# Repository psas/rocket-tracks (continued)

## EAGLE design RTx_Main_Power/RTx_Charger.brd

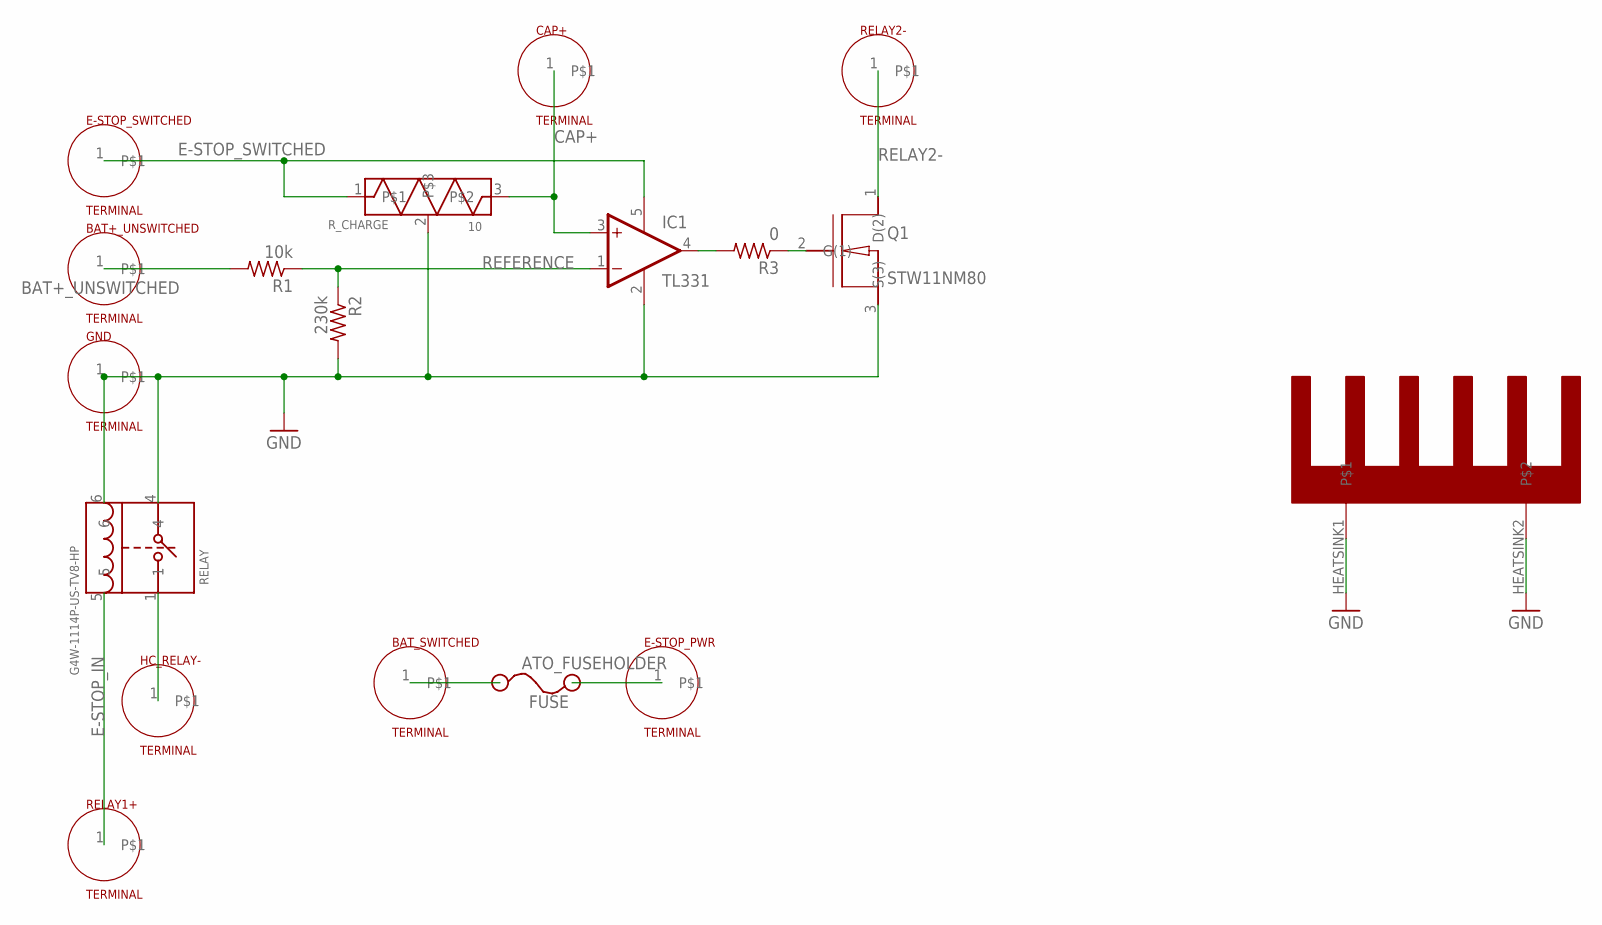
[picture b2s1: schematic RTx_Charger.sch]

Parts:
BAT+_UNSWITCHED: TERMINAL; TERMINAL_STUD
BAT_SWITCHED: TERMINAL; TERMINAL_NO-STUD
CAP+: TERMINAL; TERMINAL_STUD
E-STOP_PWR: TERMINAL; TERMINAL_STUD
E-STOP_SWITCHED: TERMINAL; TERMINAL_NO-STUD
FUSE: ATO_FUSEHOLDER; ATO_BLADE_FUSE
GND: TERMINAL; TERMINAL_STUD
HC_RELAY-: TERMINAL; TERMINAL_NO-STUD
HEATSINK: WA-T247-101E
IC1: TL331; DBV-R-PDSO-G5
Q1: STW11NM80; TO-247
R1: 10k; R1206
R2: 230k; R1206
R3: 0; R1206
RELAY: G4W-1114P-US-TV8-HP
RELAY1+, RELAY2-: TERMINAL; TERMINAL_NO-STUD
R_CHARGE: 10; TEH70

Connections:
BAT+_UNSWITCHED: BAT+_UNSWITCHED.1, R1.2
BAT_SWITCHED: BAT_SWITCHED.1, FUSE.2.1 (C), FUSE.2.2 (C), FUSE.2.3 (C), FUSE.2.4 (C)
CAP+: CAP+.1, IC1.3 (+IN), R_CHARGE.3
E-STOP_IN: RELAY.5, RELAY1+.1
E-STOP_PWR: E-STOP_PWR.1, FUSE.1.1 (A), FUSE.1.2 (A), FUSE.1.3 (A), FUSE.1.4 (A)
E-STOP_SWITCHED: E-STOP_SWITCHED.1, IC1.5 (V+), R_CHARGE.1
GND: GND.1, HEATSINK.HEATSINK1, HEATSINK.HEATSINK2, IC1.2 (GND), Q1.3 (S(3)), R2.2, RELAY.4, RELAY.6, R_CHARGE.2
HC_RELAY-: HC_RELAY-.1, RELAY.1
unnamed: IC1.4 (OUT), R3.2
unnamed: Q1.2 (G(1)), R3.1
REFERENCE: IC1.1 (-IN), R1.1, R2.1
RELAY2-: Q1.1 (D(2)), RELAY2-.1

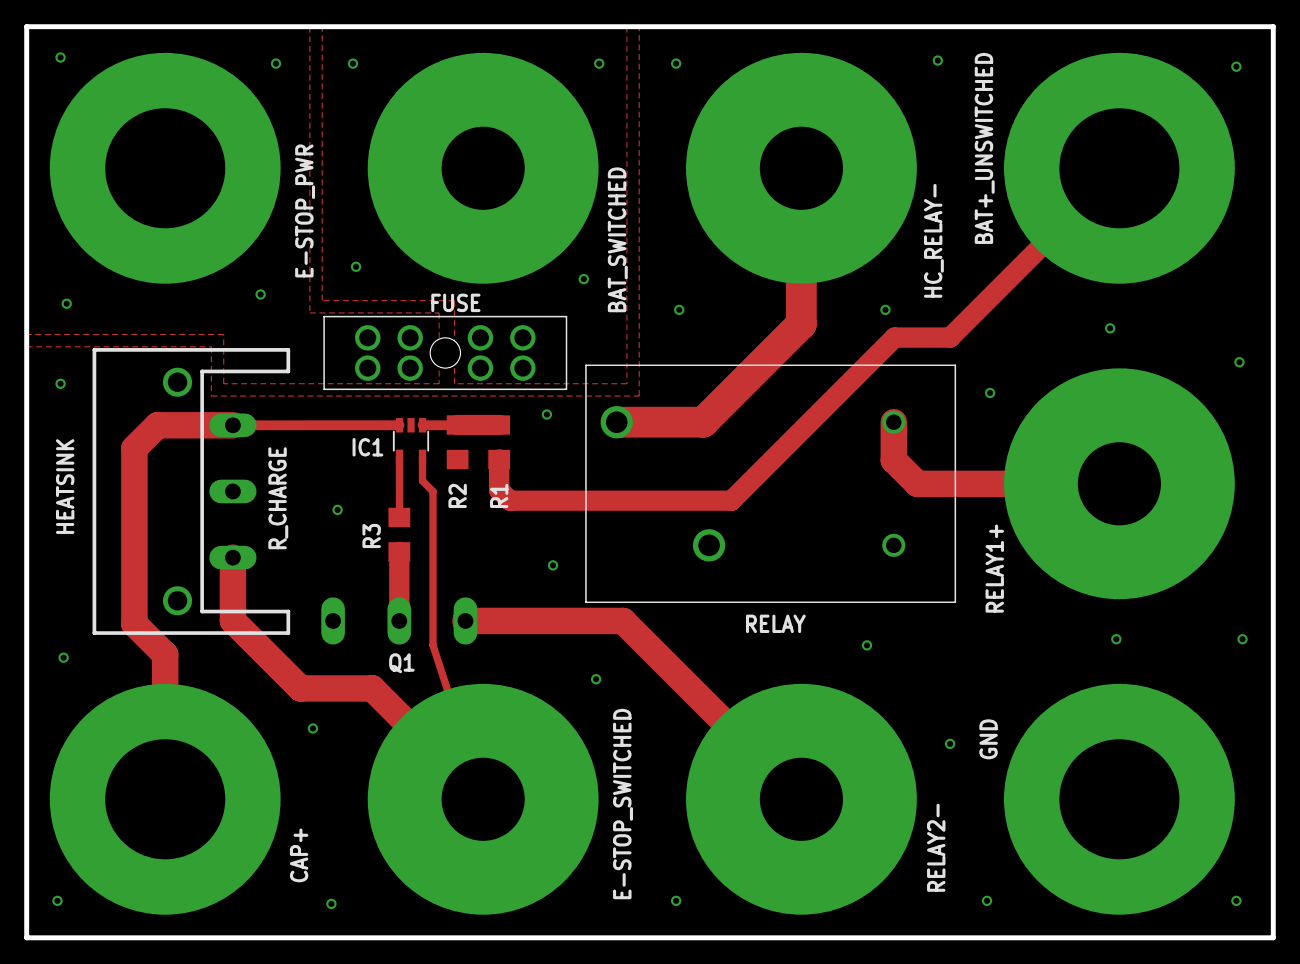
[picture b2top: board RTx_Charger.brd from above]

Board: 2 copper layers, 102.9 x 75.2 mm, 18 parts (0 on the bottom side), 12 nets.

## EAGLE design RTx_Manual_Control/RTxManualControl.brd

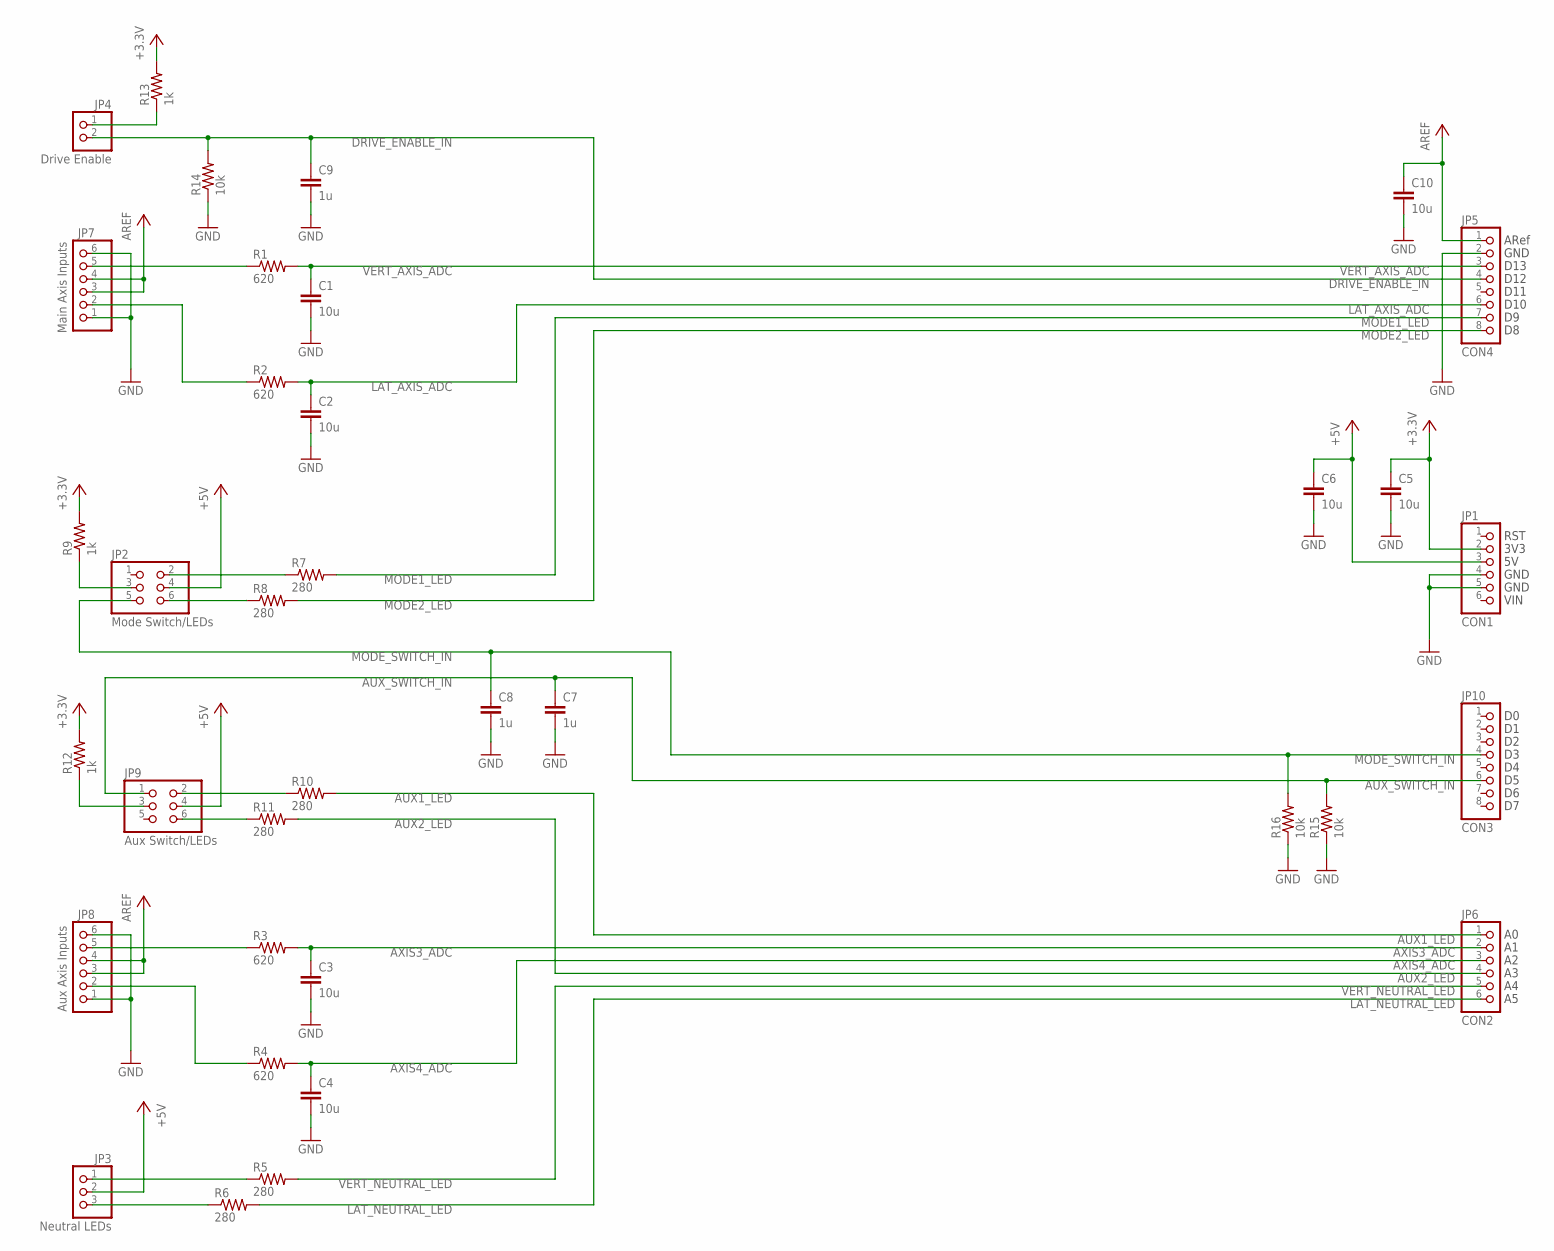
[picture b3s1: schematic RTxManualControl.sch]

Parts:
C1, C2, C3, C4, C5, C6, C10: 10u; C1206
C7, C8, C9: 1u; C1206
JP1: CON1; 1X06
JP2: Mode Switch/LEDs; 2X03
JP3: Neutral LEDs; 1X03
JP4: Drive Enable; 1X02
JP5: CON4; 1X08
JP6: CON2; 1X06
JP7: Main Axis Inputs; 1X06
JP8: Aux Axis Inputs; 1X06
JP9: Aux Switch/LEDs; 2X03
JP10: CON3; 1X08
R1, R2, R3, R4: 620; R1206
R5, R6, R7, R8, R10, R11: 280; R1206
R9, R12, R13: 1k; R1206
R14, R15, R16: 10k; R1206

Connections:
+3.3V: C5.1, JP1.2, R9.2, R12.2, R13.2
+5V: C6.1, JP1.3, JP2.4, JP3.2, JP9.4
AREF: C10.1, JP5.1, JP7.3, JP7.4, JP8.3, JP8.4
AUX1_LED: JP6.1, R10.2
AUX1_LED_CONN: JP9.2, R10.1
AUX2_LED: JP6.4, R11.2
AUX2_LED_CONN: JP9.6, R11.1
AUX_SWITCH_IN: C7.1, JP9.1, JP10.6, R15.2
AUX_SWITCH_PULLUP: JP9.3, R12.1
AXIS3_ADC: C3.1, JP6.2, R3.2
AXIS3_CONN: JP8.5, R3.1
AXIS4_ADC: C4.1, JP6.3, R4.2
AXIS4_CONN: JP8.2, R4.1
DRIVE_ENABLE_IN: C9.1, JP4.2, JP5.4, R14.2
DRIVE_ENABLE_PULLUP: JP4.1, R13.1
GND: C1.2, C2.2, C3.2, C4.2, C5.2, C6.2, C7.2, C8.2, C9.2, C10.2, JP1.4, JP1.5, JP5.2, JP7.1, JP7.6, JP8.1, JP8.6, R14.1, R15.1, R16.1
LAT_AXIS_ADC: C2.1, JP5.6, R2.2
LAT_AXIS_CONN: JP7.2, R2.1
LAT_NEAUTRAL_LED_CONN: JP3.3, R6.1
LAT_NEUTRAL_LED: JP6.6, R6.2
MODE1_LED: JP5.7, R7.2
MODE1_LED_CONN: JP2.2, R7.1
MODE2_LED: JP5.8, R8.2
MODE2_LED_CONN: JP2.6, R8.1
MODE_SWITCH_IN: C8.1, JP2.5, JP10.4, R16.2
MODE_SWITCH_PULLUP: JP2.3, R9.1
VERT_AXIS_ADC: C1.1, JP5.3, R1.2
VERT_AXIS_CONN: JP7.5, R1.1
VERT_NEUTRAL_LED: JP6.5, R5.2
VERT_NEUTRAL_LED_CONN: JP3.1, R5.1

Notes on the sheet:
ARef
GND
D13
D12
D11
D10
RST
3V3
VIN

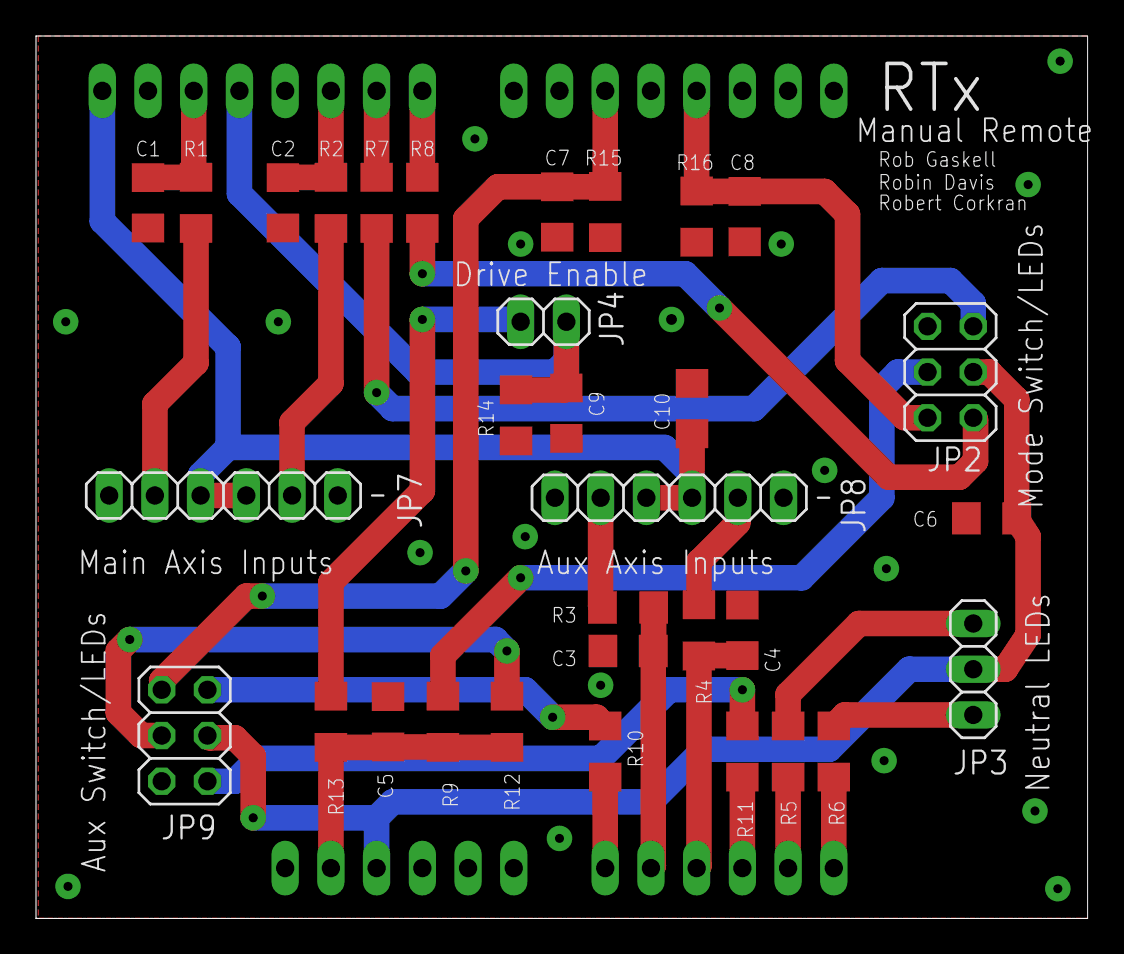
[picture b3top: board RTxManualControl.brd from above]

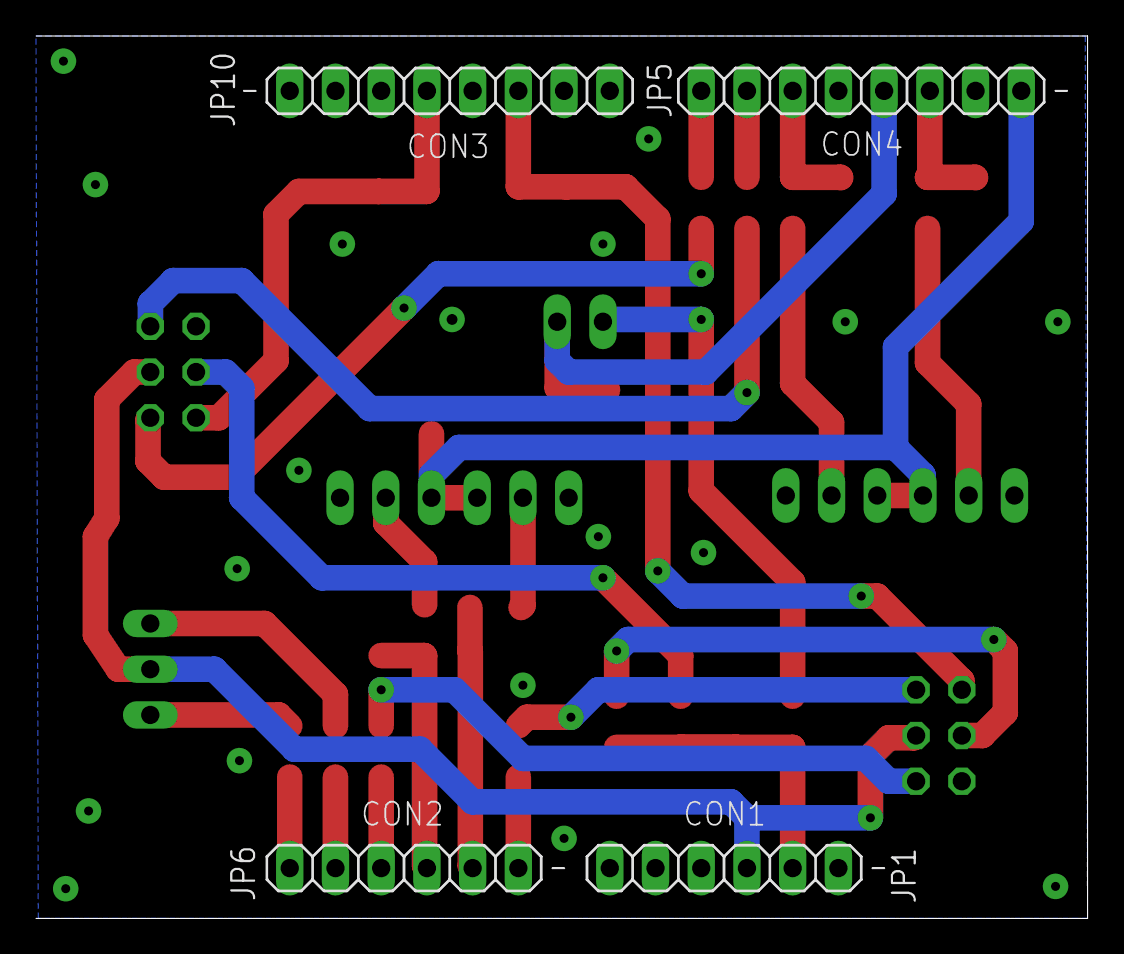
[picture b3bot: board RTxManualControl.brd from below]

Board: 2 copper layers, 58.4 x 49.0 mm, 36 parts (4 on the bottom side), 30 nets.

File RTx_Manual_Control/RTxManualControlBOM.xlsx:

RTx ID | Qty | Order PN | Value | Device | Package | Parts | Description
 | 7 |  | 10u | C-EUC1206 | C1206 | C1, C2, C3, C4, C5, C6, C10 | CAPACITOR, European symbol
 | 3 |  | 1u | C-EUC1206 | C1206 | C7, C8, C9 | CAPACITOR, European symbol
 | 3 |  | 10k | R-US_R1206 | R1206 | R14, R15, R16 | RESISTOR, American symbol
 | 3 |  | 1k | R-US_R1206 | R1206 | R9, R12, R13 | RESISTOR, American symbol
 | 6 |  | 280 | R-US_R1206 | R1206 | R5, R6, R7, R8, R10, R11 | RESISTOR, American symbol
 | 4 |  | 620 | R-US_R1206 | R1206 | R1, R2, R3, R4 | RESISTOR, American symbol
 | 2 |  |  | PINHD-1X6 | 1X06 | JP1, JP6 | PIN HEADER
 | 2 |  |  | PINHD-1X8 | 1X08 | JP5, JP10 | PIN HEADER
 | 1 |  | Drive Enable | PINHD-1X2 | 1X02 | JP4 | PIN HEADER
 | 2 |  |  | PINHD-1X6 Polarized | 1X06 | JP7, JP8 | PIN HEADER POLARIZED
 | 2 |  |  | PINHD-2X3 Polarized | 2X03 | JP2, JP9 | PIN HEADER POLARIZED
 | 1 |  | Neutral LEDs | PINHD-1X3 Polarized | 1X03 | JP3 | PIN HEADER POLARIZED

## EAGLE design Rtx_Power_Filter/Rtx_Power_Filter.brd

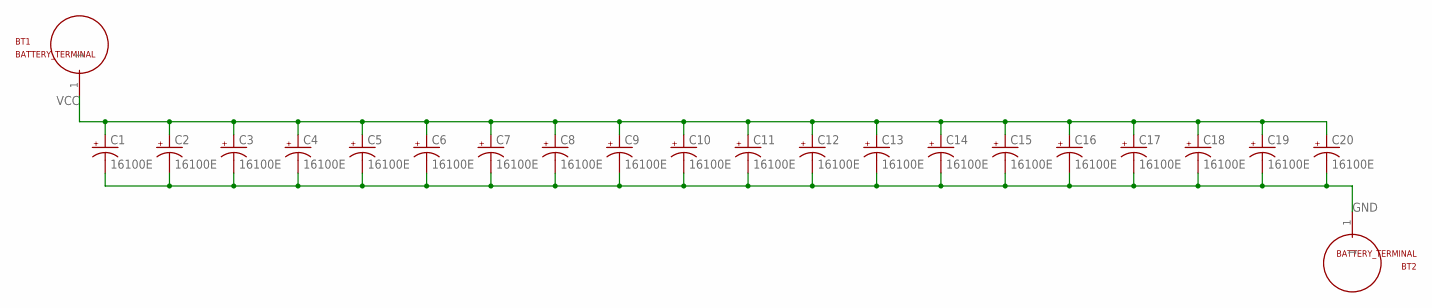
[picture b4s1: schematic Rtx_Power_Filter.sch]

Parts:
BT1, BT2: BATTERY_TERMINAL
C1, C2, C3, C4, C5, C6, C7, C8, C9, C10, C11, C12, C13, C14, C15, C16, C17, C18, C19, C20: 16100E; 16100

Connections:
GND: BT2.1, C1.-, C2.-, C3.-, C4.-, C5.-, C6.-, C7.-, C8.-, C9.-, C10.-, C11.-, C12.-, C13.-, C14.-, C15.-, C16.-, C17.-, C18.-, C19.-, C20.-
VCC: BT1.1, C1.+, C2.+, C3.+, C4.+, C5.+, C6.+, C7.+, C8.+, C9.+, C10.+, C11.+, C12.+, C13.+, C14.+, C15.+, C16.+, C17.+, C18.+, C19.+, C20.+

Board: 2 copper layers, 22 parts (0 on the bottom side), 2 nets, no tracks yet.

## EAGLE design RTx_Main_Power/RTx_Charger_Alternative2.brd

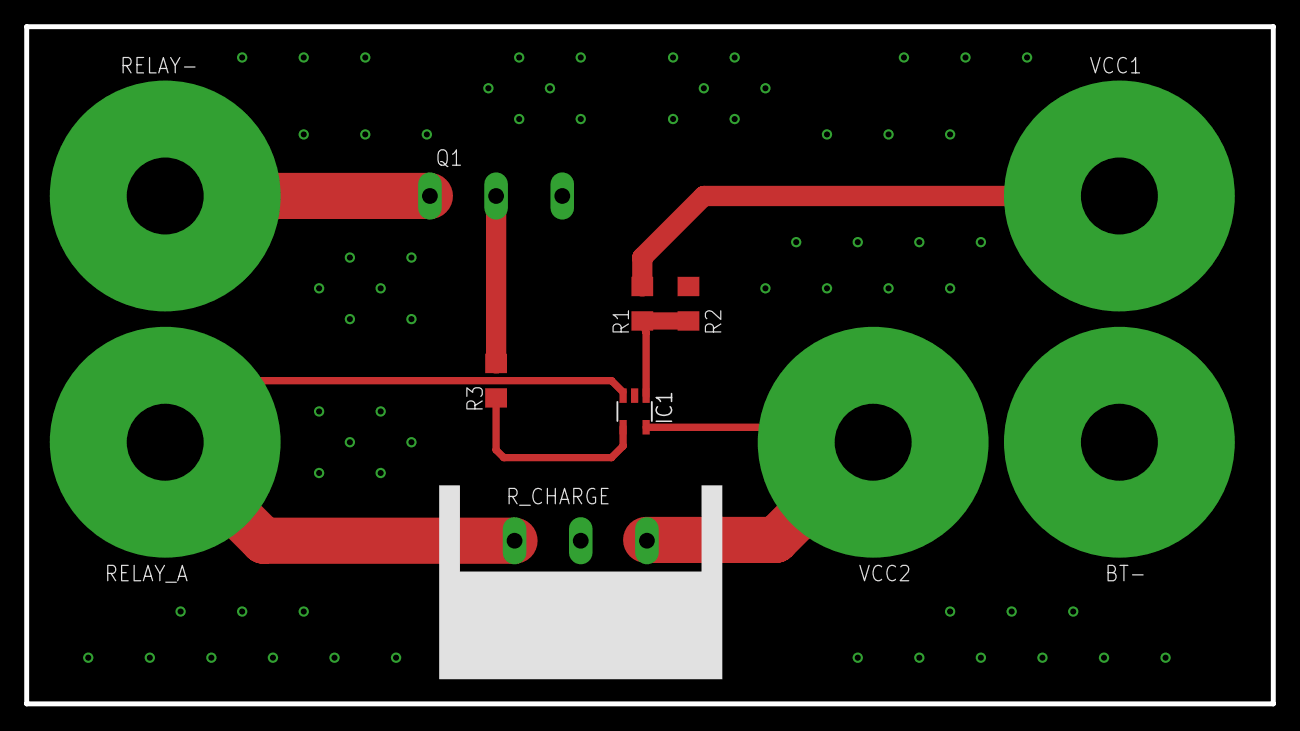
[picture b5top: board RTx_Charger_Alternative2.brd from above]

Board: 2 copper layers, 102.9 x 55.9 mm, 11 parts (0 on the bottom side), 8 nets.

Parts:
BT-: TERMINAL; TERMINAL_BATTERY
IC1: TL331; DBV-R-PDSO-G5
Q1: STW11NM80; TO-247
R1: 10k; R1206
R2: 230k; R1206
R3: 0; R1206
RELAY-: TERMINAL; TERMINAL_BATTERY
RELAY_A: TERMINAL; TERMINAL_BATTERY
R_CHARGE: 10; WA-T247-101E
VCC1, VCC2: TERMINAL; TERMINAL_BATTERY

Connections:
GND: BT-.1, IC1.2, Q1.3, R2.2, R_CHARGE.2
unnamed: IC1.4, R3.2
unnamed: Q1.2, R3.1
REFERENCE: IC1.1, R1.1, R2.1
RELAY-: Q1.1, RELAY-.1
RELAY_A: IC1.3, RELAY_A.1, R_CHARGE.3
VCC1: R1.2, VCC1.1
VCC2: IC1.5, R_CHARGE.1, VCC2.1

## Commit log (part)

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2013-11-15 Initial Check-In.
2013-11-17 Renamed Motor_Feedback folder.
2013-12-02 Initial check-in. Original LPC/GFE RocketTracks controller.
2014-01-12 Added payload module, 4th axis support. Increased connection detail.
2014-01-12 Corrected version with 4th Axis support present.
2014-01-12 Renamed Motor_Feedback_Board to RTx_Controller_Board, rocket_tracks_controller to RTx_LPC_Firmware.
2014-01-12 Moved all non-Capstone files to archive. Consolidated datasheet folders.
2014-01-15 Made initial modifications to Marketing requirements section.
2014-01-17 Removed second Ethernet PHY.
2014-01-17 Added Ethernet switch. Removed DSLR USB connection.
2014-01-17 Additions made to Marketing Requirements.
2014-01-18 Finished draft of PDS and hierarchical task list.
2014-01-21 Added dependencies to Gannt chart.
2014-01-21 Initial check-in. Added dependencies to Gantt chart.
2014-01-25 Cleaned up LPF/ADC schematic page, added 4th axis ADC support. Started LPF documentation.
2014-01-25 Initial check-in of RTx Controller Design.docx. Need explanation of ADC resolution requirements.
2014-01-25 Initial check-in. Added PDF of RTx Controller Design doc.
2014-01-27 Completed Axis Position Feedback section.
2014-01-27 Added details for ADC voltage supplies and ARef regulator.
2014-01-29 Changed ARef to 5.000V.
2014-01-29 Initial check-in. Daughter board to interface manual control box with Olimex STM32-E407 board.
2014-02-01 Completed draft of schematic without LPF component values. Need to determine LPF values, verify processor pinouts.
2014-02-02 Changed pinout of Neutral LED connector. Added supply rail decoupling cap values, ARef decoupling cap.
2014-02-02 Initial check-in. Needs Axis Manual Input section completed, and board overview description added.
2014-02-03 Added block diagram to RTx Controller Design document.
2014-02-03 Initial check-in of pre-Capstone documents.
2014-02-04 Initial check-in. New FMEA folder containing FMEA documentation. Added the most recent WPR and the most recent Gantt chart.
2014-02-04 Distributed FMEA tasks. Transferred Sightline API development to Robert.
2014-02-05 Updated PDS
2014-02-05 Initial check-in datasheet for USB ESD protection. Added initial USB setup to schematic.
2014-02-06 Initial check-in of datasheet for USB ESD protection (better component selected). Updated USB in hardware to incorperate new esd chip.
2014-02-08 Added Ethernet components to library.
2014-02-08 Development of Ethernet PHY.
2014-02-08 Updated WPR.
2014-02-09 Added USB section to documentation. Adjusted schedule slightly due to my delay from traveling.
2014-02-09 Removed irrelevant sections from Manual Input ADC section.
2014-02-10 Added MagJack port to Eagle library.
2014-02-12 Updated Ethernet PHY components and schematic.
2014-02-13 updated FMEA
2014-02-14 Completed FMEA of manual remote
2014-02-15 Updated Robert's schedule.
2014-02-16 Initial check-in. Solved equations of motion for each axis.
2014-02-16 updated WPR.Updated RTx manual remote PCB.
2014-02-16 Added Kinetic Diagrams for each axis. Corrected moment of inertia terms.
2014-02-17 Completed board layout. Ready for design review.
2014-02-17 Initial check-in. Rework of dynamics with friction, coupling.
2014-02-17 Corrected equation for lateral axis moment due to coupling with vertical axis motion.
2014-02-17 Added Ethernet pinouts to MCU.
2014-02-18 adjusted schedule to account for unexpected midterms this week. changed drill size on vias for manual controller board.
2014-02-18 Added dynamic coupling to vertical axis, solved for new PID coefficients. Higher-order terms have coefficients != 1, will this be a problem?
2014-02-19 Solved system transfer function for Vertical Axis with dynamic coupling. Can't solve Plant transfer function for lateral axis with dynamic coupling.
2014-02-20 fixed format of controller documentation
2014-02-20 updated project schedule
2014-02-20 Fixed stop mask on vias. Updated FMEA for R14.
2014-02-21 Added CPU to schematic, completed pin-out of GMD signals, Ethernet signals, USB signals. Needs JTAG connector, ESD protection.
2014-02-21 Initial check-in of Rtx_power_filter. Updated schedule reflecting meeting 2/20. Updated silkscreen on manual remote board.
2014-02-22 Replaced design rules for OshPark.
2014-02-23 Completed RTx Power Filter Board.
2014-02-24 Added LPF to transfer function. Need method to solve for PID coefficients.
2014-02-25 Added values for manual input LPF components. Completed RTx Manual Remote Design document.
2014-02-26 Added PoE power supply to controller board.
2014-02-26 Made the bplace text the right way.
2014-02-26 Changed values to place layers for header labels.
2014-02-26 Generated BOM for Manual Control board. Corrected capacitor value formatting.
2014-02-26 Added partial list of Digikey part numbers.
2014-02-26 Added headers/socket part numbers.
2014-02-27 Completed RTxManualControlBOM.xlsx for order.
2014-02-27 Updated schedule to reflect changes in battery subsystem.
2014-02-28 Added 8V power supply. Updated Ethernet documentation.
2014-03-01 last weeks WPR update.
2014-03-02 WPR updated.
2014-03-05 Added SWD connector, values for output pin ESD protection components.
2014-03-05 Simulations for ESD protection circuits.
2014-03-05 Solved for PID gains with LPF term factored into transfer function.
2014-03-08 Updated WPR.docx
2014-03-11 Added capacitance to 8V and 48V PoE power supplies. Need to verify SPI daisy-chain pinout.
2014-03-11 Work on FMEA of RTx Controller Schematic
2014-03-13 Began solving for numeric gain values. Need C_F, and need to resolve complex values.
2014-03-13 Updates made to FMEA.
2014-03-15 Made modifications to address issues recorded and closed.
2014-03-16 WPR for 3/14/14
2014-03-18 Closed issues related to Power page of schematic.
2014-03-18 Cleaned up schematic, began layout of RTx Controller PCB.
2014-03-20 Added documentation for Microcontroller.
2014-03-21 minor updates made to USB documentation and FMEA.
2014-03-22 Submitted WPR.docx for this week.
2014-03-24 Updated FMEA. Updated USB on schematic to include border. Updated documentation on USB.
2014-03-26 Updated FMEA.
2014-03-27 Solved numeric value for integral gain for theta_l = pi/2. Result is imaginary.
2014-03-28 Added charger schematic and board along with part datasheets.
2014-03-28 Added power supply table to schematic. Modified various components to be surface mount.
2014-03-28 Included power supply table.
2014-03-28 Revert "Added power supply table to schematic. Modified various components to be surface mount."
    This reverts commit e3ac1e6c28b3b33263b1681ea2489635cc48a7dc.
2014-03-28 Revert "Added charger schematic and board along with part datasheets."
    This reverts commit c83723e76ca39845fbcdc11e1f686fe063c81314.
2014-03-28 Precharge circuit and datasheets.
2014-03-30 updated layout of Rtx Controller Board.
2014-03-31 Most recent WPR.docx. Updated charger circuit to reflect potential issue fix.
2014-04-01 LTSpice main power charging circuit.
2014-04-01 Proposed solution eliminating all but the high-current relay which bypasses the charge resistor.
2014-04-01 Updated power supply documentation. Included alternative charger schematic.
2014-04-01 Ethernet and PoE controllers completely redone.
2014-04-02 Ethernet pinout.
2014-04-02 Added LEDs and testpoints to processor for debugging. Fixed JTAG connector.
2014-04-03 Updated USB portion of schematic to include crystal and fixed capacitance. Initial check in of crystal datasheet.
2014-04-03 Updated block diagram to reflect RTx Controller design.
2014-04-04 Solved for example numerical gains.
2014-04-04 Plotted root locus for example gain and moment of inertia values.
2014-04-04 Added rlocus for lat axis.
2014-04-04 Ethernet section of RTx Controller Design document redone to reflect newly incorporated components.
2014-04-04 Ethernet section of RTx Controller Design document redone to reflect recently replaced components.
2014-04-04 Added folder for Sightline data.
2014-04-04 Sightline tracking sample video.
2014-04-04 Added MATLAB scripts, updated RTxController.pdf.
2014-04-04 small changes made to layout.
2014-04-05 updates made to PCB layout
2014-04-05 Added voltage divider to inverting input of opamp.
2014-04-06 Updated schedule.
2014-04-07 Updated WPR document and schedule.
2014-04-08 Updated controller schematic with high speed signal routing information. Added termination resistor to SPI_SCK line. Included Sightline documentation. Added avionics library, node4-2.lbr, to RTx cont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
2014-04-10 Changes to RTx charger board.
2014-04-10 updates made to RTx layout
2014-04-10 minor updates made
2014-04-12 Updated WPR and schedule. Updated system block diagram. Completed firmware GPIO details.
2014-04-13 Rtx Controller board updated, all that remains are power planes and rework by Rob. Initial check in of crystal.lbr.
2014-04-13 Repositioned LDO's created power planes.
2014-04-14 High speed signal routing information added to schematic. Updated Precharge board.
2014-04-15 Added termination resistors to RMII bus, adjusted width of digital signals.
2014-04-15 Created RTx Charger BOM.
2014-04-15 Reduced board width.
2014-04-15 Updated schematic PDF, created layout PDF.
2014-04-16 PoE power supply ON/OFF connection changed to open circuit, to remain ON.
2014-04-16 Additional RTx Controller layout performed.
2014-04-18 Cleared all non-ground airwires, replaced dual LDO with 3.3V and 5V LDO's, reconfigured power planes.
2014-04-18 Added "temp_library.lbr" to eagle folder. Updated Power requirements excel documentation.
2014-04-19 Board layout ready for design review.
2014-04-19 Updated parts in temp_library.lbr (RJ45, 8V power supply, and 48V power supply).
2014-04-19 Closed additional issues raised in layout review.
2014-04-19 Layout ready for silkscreen cleanup. Updated schedule.
2014-04-20 Updated Rtx Controller silkscreen
2014-04-20 Closed all remaining issues from layout review.
2014-04-22 Added drawing of E-Stop control circuit for addition to Main Power board.
2014-04-23 Replaced non-existent capacitors with available parts.
2014-04-23 Initial check-in of Controller Board BOM.
2014-04-23 Updated controller board BOM part numbers.
2014-04-24 Added Robin's part #'s. Needs MAXIM POE Controller supplier.
2014-04-24 Added E-Stop circuit to Main Power board.
2014-04-25 Added TP to Pin 6 of POE Controller.
2014-04-25 Changed PoE controller to variant A.
2014-04-25 Final commit for order.
2014-04-25 Changed font to vector, 25 mils, 20% -- now go fix all the prettiness.
2014-04-25 Added additional terminals to RTx_Charger board.
2014-04-25 Added terminals for connectors to BOM.
2014-04-25 Indicated firewall stud connections.
2014-04-25 updated RTx Controller Board silkscreen.
2014-04-25 Fixed page breaks.
2014-04-25 Text fixed and ready to order.
2014-04-25 RTx_Charger board layout changed.
2014-04-26 Completed charger board and BOM.
2014-04-26 Charger board completed.
2014-04-26 Added panel-mount D-Sub to BOM.
2014-04-26 Removed video from sightline folder.
2014-05-02 Updated project schedule.
2014-05-09 Added packet information captured by wireshark to Sightline folder.
2014-05-13 Created test plan document.
2014-05-15 Initial check in of System FMEA. Updated signal names to match system FMEA in schematic.
2014-05-16 Added gerber files for RTx Controller stencil.
2014-05-17 Initial check-in of poster materials. updated FMEA
2014-05-22 added example poster
2014-05-23 updated presentation
2014-05-24 updated poster
2014-05-26 Block diagram for poster.
2014-05-26 Poster rough draft
2014-05-26 poster rough draft (poster2)
2014-05-26 Updated poster2 power point.
2014-05-28 Added pictures of the RTx controller board.
2014-05-29 final poster
2014-06-03 Precharge circuit spice schematic labeled with Eagle schematic labels.
2014-06-09 UPdated documentation to state USB ESD protection chip removal. Initial check-in of final report for Jeske.
2014-06-10 initial check in of power point
2014-06-11 presentation update
2014-06-11 presentation updated again
2014-06-11 Precharge documentation.
2014-06-12 Completed RTX Controller Firmware documentation.
2014-06-12 Completed documentation for Capstone.
2014-06-12 Reorganized documentation folder.
